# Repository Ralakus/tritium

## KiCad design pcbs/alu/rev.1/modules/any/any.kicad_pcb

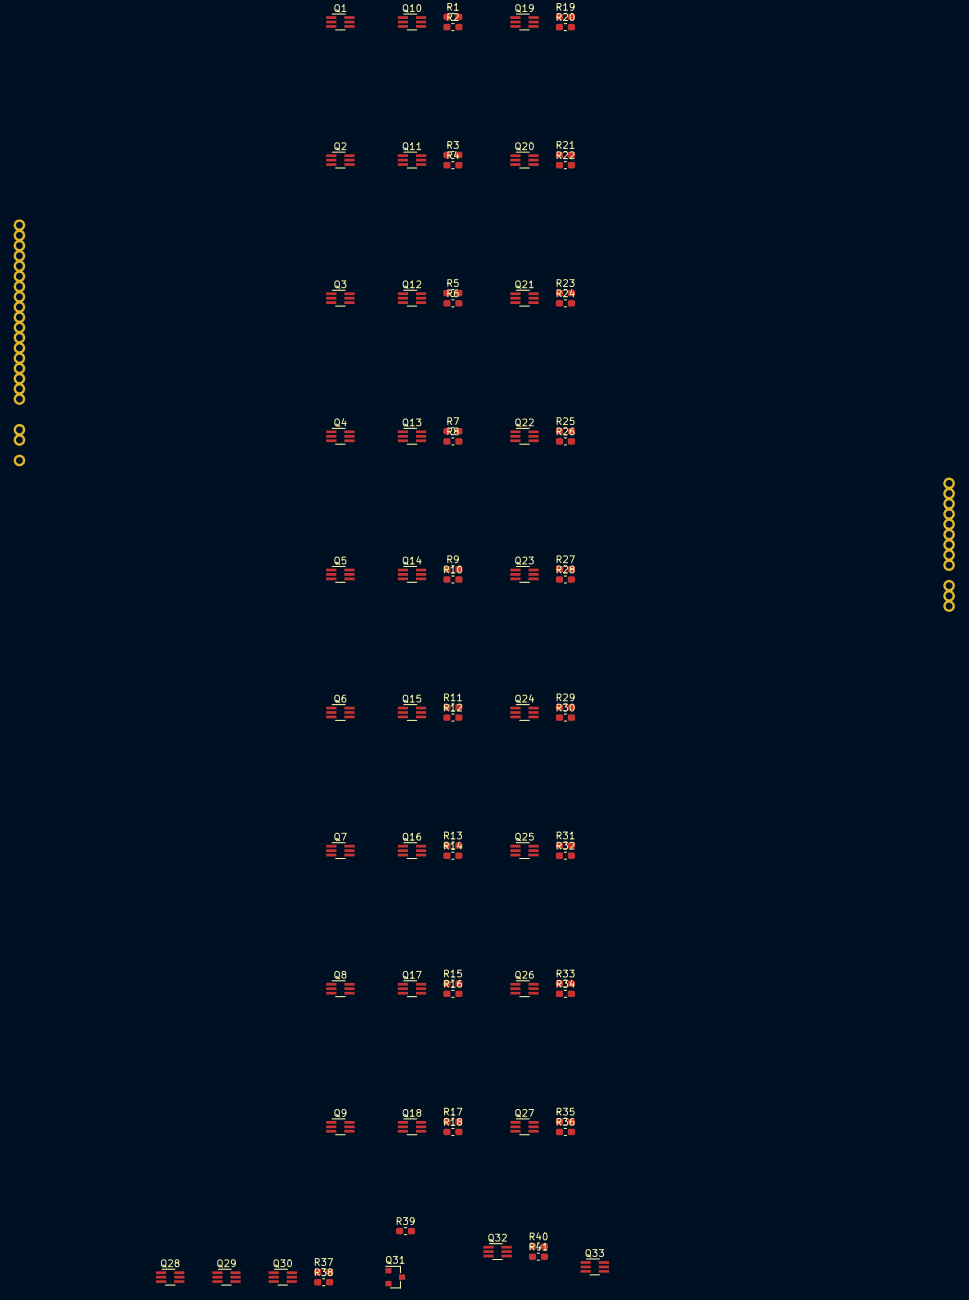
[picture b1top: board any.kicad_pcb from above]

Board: 2 copper layers, 107 parts (0 on the bottom side), 105 nets, no tracks yet.

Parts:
J1, J2, J3, J4, J5, J6, J7, J8, J9, J10, J11, J12, J13, J14, J15, J16, J17, J18, J19, J20, J21, J22, J23, J24, J25, J26, J27, J28, J29, J30, J31, J32, J33: Conn_01x01; Edge_Castellation_1x01_P2.54
Q1, Q2, Q3, Q4, Q5, Q6, Q7, Q8, Q9, Q10, Q11, Q12, Q13, Q14, Q15, Q16, Q17, Q18, Q19, Q20, Q21, Q22, Q23, Q24, Q25, Q26, Q27, Q28, Q29, Q30, Q32, Q33: BSS8402DW; SOT-363_SC-70-6_Handsoldering
Q31: 2N7002; SOT-23
R1, R2, R3, R4, R5, R6, R7, R8, R9, R10, R11, R12, R13, R14, R15, R16, R17, R18, R19, R20, R21, R22, R23, R24, R25, R26, R27, R28, R29, R30, R31, R32, R33, R34, R35, R36, R37, R38, R39, R40, R41: 12k; R_0603_1608Metric_Pad1.05x0.95mm_HandSolder

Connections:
/Sheet5FFC6CCC/Vdd: Q1.4, Q2.4, Q3.4, Q4.4, Q5.4, Q6.4, Q7.4, Q8.4, Q9.4, Q19.4, Q20.4, Q21.4, Q22.4, Q23.4, Q24.4, Q25.4, Q26.4, Q27.4, Q33.3
/Sheet5FFC6CCC/Vss: Q1.1, Q2.1, Q3.1, Q4.1, Q5.1, Q6.1, Q7.1, Q8.1, Q9.1, Q19.1, Q20.1, Q21.1, Q22.1, Q23.1, Q24.1, Q25.1, Q26.1, Q27.1, Q33.6
A0: J1.1, Q9.2, Q9.5
A1: J2.1, Q8.2, Q8.5
A2: J3.1, Q7.2, Q7.5
A3: J4.1, Q6.2, Q6.5
A4: J5.1, Q5.2, Q5.5
A5: J6.1, Q4.2, Q4.5
A6: J7.1, Q3.2, Q3.5
A7: J8.1, Q2.2, Q2.5
A8: J9.1, Q1.2, Q1.5
B0: J10.1, Q18.2, Q18.5
B1: J11.1, Q17.2, Q17.5
B2: J12.1, Q16.2, Q16.5
B3: J13.1, Q15.2, Q15.5
B4: J14.1, Q14.2, Q14.5
B5: J15.1, Q13.2, Q13.5
B6: J16.1, Q12.2, Q12.5
B7: J17.1, Q11.2, Q11.5
B8: J18.1, Q10.2, Q10.5
FnA2: J19.1, Q28.2, Q28.5
FnB2: J20.1, Q29.2, Q29.5
GND: J32.1, Q31.2
unnamed: Q1.3, Q10.4
unnamed: Q1.6, Q10.1
unnamed: Q10.3, R1.2
unnamed: Q10.6, R2.1
unnamed: Q2.6, Q11.1
unnamed: Q11.3, R3.2
unnamed: Q2.3, Q11.4
unnamed: Q11.6, R4.1
unnamed: Q3.6, Q12.1
unnamed: Q12.3, R5.2
unnamed: Q3.3, Q12.4
unnamed: Q12.6, R6.1
unnamed: Q4.6, Q13.1
unnamed: Q13.3, R7.2
unnamed: Q4.3, Q13.4
unnamed: Q13.6, R8.1
unnamed: Q5.6, Q14.1
unnamed: Q14.3, R9.2
unnamed: Q5.3, Q14.4
unnamed: Q14.6, R10.1
unnamed: Q6.6, Q15.1
unnamed: Q15.3, R11.2
unnamed: Q6.3, Q15.4
unnamed: Q15.6, R12.1
unnamed: Q7.6, Q16.1
unnamed: Q16.3, R13.2
unnamed: Q7.3, Q16.4
unnamed: Q16.6, R14.1
unnamed: Q8.6, Q17.1
unnamed: Q17.3, R15.2
unnamed: Q8.3, Q17.4
unnamed: Q17.6, R16.1
unnamed: Q9.6, Q18.1
unnamed: Q18.3, R17.2
unnamed: Q9.3, Q18.4
unnamed: Q18.6, R18.1
unnamed: Q19.2, Q19.5, R1.1, R2.2
unnamed: Q19.3, R19.2
unnamed: Q19.6, R20.1
unnamed: Q20.2, Q20.5, R3.1, R4.2
unnamed: Q20.3, R21.2
unnamed: Q20.6, R22.1
unnamed: Q21.2, Q21.5, R5.1, R6.2
unnamed: Q21.3, R23.2
unnamed: Q21.6, R24.1
unnamed: Q22.2, Q22.5, R7.1, R8.2
unnamed: Q22.3, R25.2
unnamed: Q22.6, R26.1
unnamed: Q23.2, Q23.5, R9.1, R10.2
unnamed: Q23.3, R27.2
unnamed: Q23.6, R28.1
unnamed: Q24.2, Q24.5, R11.1, R12.2
unnamed: Q24.3, R29.2
unnamed: Q24.6, R30.1
unnamed: Q25.2, Q25.5, R13.1, R14.2
unnamed: Q25.3, R31.2
unnamed: Q25.6, R32.1
unnamed: Q26.2, Q26.5, R15.1, R16.2
unnamed: Q26.3, R33.2
unnamed: Q26.6, R34.1
unnamed: Q27.2, Q27.5, R17.1, R18.2
unnamed: Q27.3, R35.2
unnamed: Q27.6, R36.1
unnamed: Q28.3, Q29.3, Q30.3, R37.2
unnamed: Q28.6, Q29.6, Q30.6, R38.1
unnamed: Q31.1, R37.1, R38.2
unnamed: Q31.3, Q32.2, Q32.5, Q33.2, R39.1
unnamed: Q32.3, R40.2
unnamed: Q32.6, R41.1
unnamed: Q33.5, R40.1, R41.2
OutputEnable: J21.1, Q30.2, Q30.5
R0: J22.1, R35.1, R36.2
R1: J23.1, R33.1, R34.2
R2: J24.1, R31.1, R32.2
R3: J25.1, R29.1, R30.2
R4: J26.1, R27.1, R28.2
R5: J27.1, R25.1, R26.2
R6: J28.1, R23.1, R24.2
R7: J29.1, R21.1, R22.2
R8: J30.1, R19.1, R20.2
Vdd: J31.1, Q28.4, Q29.4, Q30.4, Q32.4, Q33.4, R39.2
Vss: J33.1, Q28.1, Q29.1, Q30.1, Q32.1, Q33.1

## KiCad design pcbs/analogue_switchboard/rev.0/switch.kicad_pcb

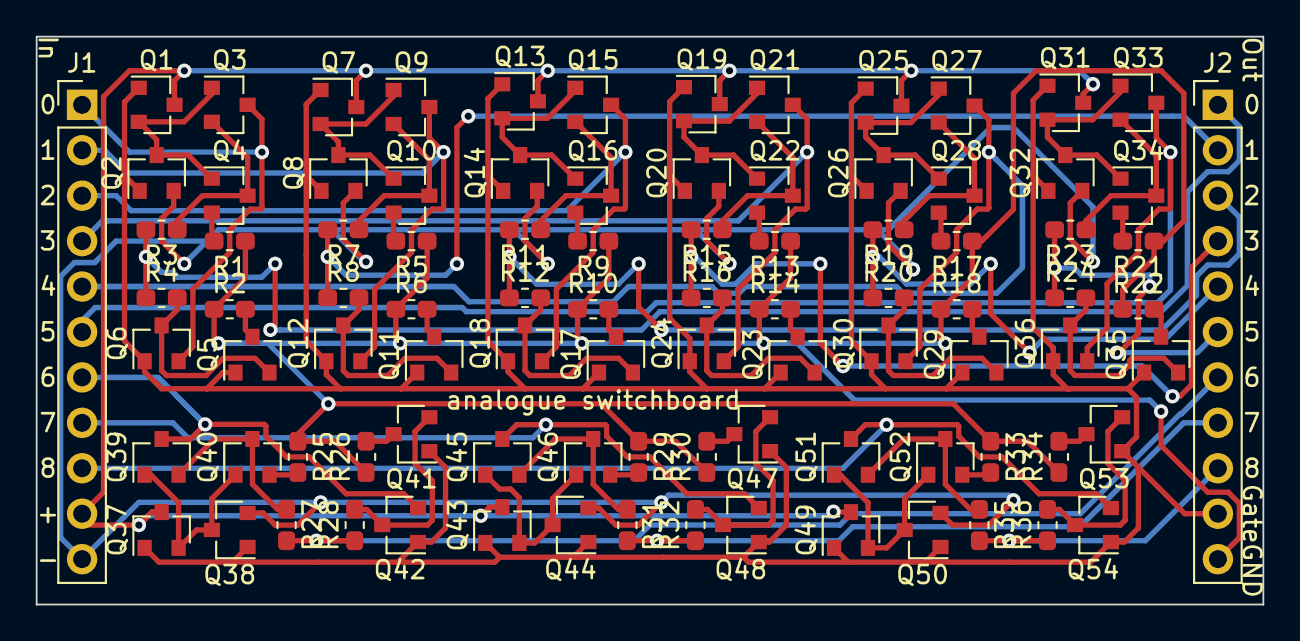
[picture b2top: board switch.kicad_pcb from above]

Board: 2 copper layers, 68.6 x 31.8 mm, 92 parts (0 on the bottom side), 67 nets.

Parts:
J1, J2: Conn_01x11; PinHeader_1x11_P2.54mm_Vertical
Q1, Q3, Q4, Q7, Q9, Q10, Q13, Q15, Q16, Q19, Q21, Q22, Q25, Q27, Q28, Q31, Q33, Q34, Q37, Q39, Q40, Q43, Q45, Q46, Q49, Q51, Q52: BSS84; SOT-23
Q2, Q5, Q6, Q8, Q11, Q12, Q14, Q17, Q18, Q20, Q23, Q24, Q26, Q29, Q30, Q32, Q35, Q36, Q38, Q41, Q42, Q44, Q47, Q48, Q50, Q53, Q54: 2N7002; SOT-23
R1, R2, R3, R4, R5, R6, R7, R8, R9, R10, R11, R12, R13, R14, R15, R16, R17, R18, R19, R20, R21, R22, R23, R24, R25, R26, R27, R28, R29, R30, R31, R32, R33, R34, R35, R36: 12k; R_0603_1608Metric_Pad1.05x0.95mm_HandSolder

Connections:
GND: J2.11, R1.1, R2.1, R5.1, R6.1, R9.1, R10.1, R13.1, R14.1, R17.1, R18.1, R21.1, R22.1, R25.1, R26.1, R29.1, R30.1, R33.1, R34.1
Gate: J2.10, Q1.1, Q2.1, Q5.1, Q6.1, Q7.1, Q8.1, Q11.1, Q12.1, Q13.1, Q14.1, Q17.1, Q18.1, Q19.1, Q20.1, Q23.1, Q24.1, Q25.1, Q26.1, Q29.1, Q30.1, Q31.1, Q32.1, Q35.1, Q36.1, Q37.1, Q38.1, Q41.1, Q42.1, Q43.1, Q44.1, Q47.1, Q48.1, Q49.1, Q50.1, Q53.1, Q54.1
I0: J1.1, Q3.3, Q6.2
I1: J1.2, Q9.3, Q12.2
I2: J1.3, Q15.3, Q18.2
I3: J1.4, Q21.3, Q24.2
I4: J1.5, Q27.3, Q30.2
I5: J1.6, Q33.3, Q36.2
I6: J1.7, Q39.3, Q42.2
I7: J1.8, Q45.3, Q48.2
I8: J1.9, Q51.3, Q54.2
unnamed: Q1.2, Q2.3, Q3.1, Q4.1
unnamed: Q3.2, Q4.3, R3.1
unnamed: Q4.2, R1.2
unnamed: Q5.2, Q6.3, R4.2
unnamed: Q5.3, R2.2
unnamed: Q7.2, Q8.3, Q9.1, Q10.1
unnamed: Q10.2, R5.2
unnamed: Q9.2, Q10.3, R7.1
unnamed: Q11.2, Q12.3, R8.2
unnamed: Q11.3, R6.2
unnamed: Q13.2, Q14.3, Q15.1, Q16.1
unnamed: Q15.2, Q16.3, R11.1
unnamed: Q16.2, R9.2
unnamed: Q17.2, Q18.3, R12.2
unnamed: Q17.3, R10.2
unnamed: Q19.2, Q20.3, Q21.1, Q22.1
unnamed: Q21.2, Q22.3, R15.1
unnamed: Q22.2, R13.2
unnamed: Q23.2, Q24.3, R16.2
unnamed: Q23.3, R14.2
unnamed: Q25.2, Q26.3, Q27.1, Q28.1
unnamed: Q27.2, Q28.3, R19.1
unnamed: Q28.2, R17.2
unnamed: Q29.2, Q30.3, R20.2
unnamed: Q29.3, R18.2
unnamed: Q31.2, Q32.3, Q33.1, Q34.1
unnamed: Q33.2, Q34.3, R23.1
unnamed: Q34.2, R21.2
unnamed: Q35.2, Q36.3, R24.2
unnamed: Q35.3, R22.2
unnamed: Q37.2, Q38.3, Q39.1, Q40.1
unnamed: Q39.2, Q40.3, R27.1
unnamed: Q40.2, R25.2
unnamed: Q41.2, Q42.3, R28.2
unnamed: Q41.3, R26.2
unnamed: Q43.2, Q44.3, Q45.1, Q46.1
unnamed: Q45.2, Q46.3, R31.1
unnamed: Q46.2, R29.2
unnamed: Q47.2, Q48.3, R32.2
unnamed: Q47.3, R30.2
unnamed: Q49.2, Q50.3, Q51.1, Q52.1
unnamed: Q51.2, Q52.3, R35.1
unnamed: Q52.2, R33.2
unnamed: Q53.2, Q54.3, R36.2
unnamed: Q53.3, R34.2
O0: J2.1, R3.2, R4.1
O1: J2.2, R7.2, R8.1
O2: J2.3, R11.2, R12.1
O3: J2.4, R15.2, R16.1
O4: J2.5, R19.2, R20.1
O5: J2.6, R23.2, R24.1
O6: J2.7, R27.2, R28.1
O7: J2.8, R31.2, R32.1
O8: J2.9, R35.2, R36.1
Vdd: J1.10, Q1.3, Q7.3, Q13.3, Q19.3, Q25.3, Q31.3, Q37.3, Q43.3, Q49.3
Vss: J1.11, Q2.2, Q8.2, Q14.2, Q20.2, Q26.2, Q32.2, Q38.2, Q44.2, Q50.2

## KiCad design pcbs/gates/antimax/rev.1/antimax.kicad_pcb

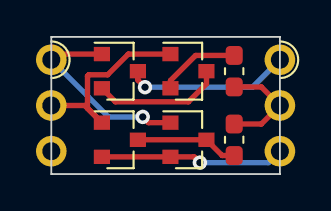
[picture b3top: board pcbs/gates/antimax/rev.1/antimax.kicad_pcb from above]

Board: 2 copper layers, 12.7 x 7.6 mm, 8 parts (0 on the bottom side), 8 nets.

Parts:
J1, J2: Conn_01x03; Edge_Castellation_1x03_P2.54
Q1, Q4: 2N7002; SOT-23
Q2, Q3: BSS84; SOT-23
R1, R2: 12k; R_0603_1608Metric_Pad1.05x0.95mm_HandSolder

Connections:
A: J1.1, Q2.1, Q4.1
B: J1.2, Q1.1, Q3.1
unnamed: Q1.3, Q4.3, R2.2
unnamed: Q2.2, Q3.3
unnamed: Q3.2, R1.1
Out: J2.2, R1.2, R2.1
Vdd: J2.1, Q2.3
Vss: J2.3, Q1.2, Q4.2

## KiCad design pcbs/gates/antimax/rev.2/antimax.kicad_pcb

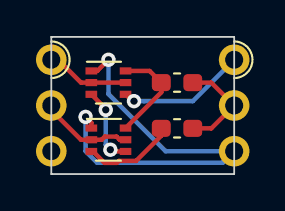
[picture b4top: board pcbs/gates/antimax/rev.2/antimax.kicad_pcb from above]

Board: 2 copper layers, 10.2 x 7.6 mm, 6 parts (0 on the bottom side), 8 nets.

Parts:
J1, J2: Conn_01x03; Edge_Castellation_1x03_P2.54
Q1, Q2: BSS8402DW; SOT-363_SC-70-6
R1, R2: 12k; R_0603_1608Metric_Pad1.05x0.95mm_HandSolder

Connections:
A: J1.1, Q1.2, Q1.5
B: J1.2, Q2.2, Q2.5
unnamed: Q1.3, Q2.4
unnamed: Q1.6, Q2.6, R2.2
unnamed: Q2.3, R1.1
Out: J2.2, R1.2, R2.1
Vdd: J2.1, Q1.4
Vss: J2.3, Q1.1, Q2.1

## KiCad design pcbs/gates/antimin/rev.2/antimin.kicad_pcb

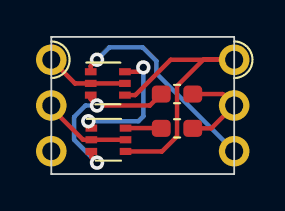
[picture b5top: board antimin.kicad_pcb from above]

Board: 2 copper layers, 10.2 x 7.6 mm, 6 parts (0 on the bottom side), 8 nets.

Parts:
J1, J2: Conn_01x03; Edge_Castellation_1x03_P2.54
Q1, Q2: BSS8402DW; SOT-363_SC-70-6
R1, R2: 12k; R_0603_1608Metric_Pad1.05x0.95mm_HandSolder

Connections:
A: J1.1, Q1.2, Q1.5
B: J1.2, Q2.2, Q2.5
unnamed: Q1.3, Q2.3, R1.1
unnamed: Q1.6, Q2.1
unnamed: Q2.6, R2.2
Out: J2.2, R1.2, R2.1
Vdd: J2.1, Q1.4, Q2.4
Vss: J2.3, Q1.1

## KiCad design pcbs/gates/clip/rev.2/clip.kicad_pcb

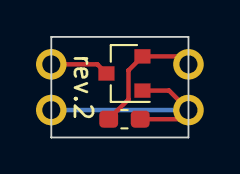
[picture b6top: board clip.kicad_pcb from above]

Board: 2 copper layers, 7.6 x 5.6 mm, 6 parts (0 on the bottom side), 3 nets.

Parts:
J1, J2, J3, J4: Conn_01x01; Edge_Castellation_1x01_P2.54
Q1: BSS84; SOT-23
R1: 470k; R_0603_1608Metric_Pad1.05x0.95mm_HandSolder

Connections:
Anode: J1.1, Q1.3
Cathode: J3.1, Q1.2, R1.1
GND: J2.1, J4.1, Q1.1, R1.2

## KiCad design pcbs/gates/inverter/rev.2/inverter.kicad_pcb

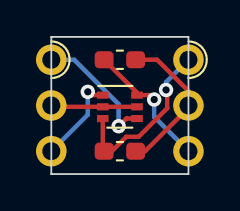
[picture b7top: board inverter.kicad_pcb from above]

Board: 2 copper layers, 7.6 x 7.6 mm, 5 parts (0 on the bottom side), 6 nets.

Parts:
J1, J2: Conn_01x03; Edge_Castellation_1x03_P2.54
Q1: BSS8402DW; SOT-363_SC-70-6
R1, R2: 12k; R_0603_1608Metric_Pad1.05x0.95mm_HandSolder

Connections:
In: J1.2, Q1.2, Q1.5
Nti: J2.3, Q1.6, R2.2
Out: J2.2, R1.2, R2.1
Pti: J2.1, Q1.3, R1.1
Vdd: J1.1, Q1.4
Vss: J1.3, Q1.1

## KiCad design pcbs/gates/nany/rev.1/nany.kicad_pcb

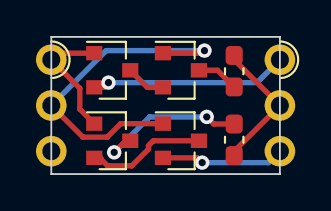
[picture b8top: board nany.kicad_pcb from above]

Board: 2 copper layers, 12.7 x 7.6 mm, 8 parts (0 on the bottom side), 9 nets.

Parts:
J1, J2: Conn_01x03; Edge_Castellation_1x03_P2.54
Q1, Q2: BSS84; SOT-23
Q3, Q4: 2N7002; SOT-23
R1, R2: 12k; R_0603_1608Metric_Pad1.05x0.95mm_HandSolder

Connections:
A: J1.1, Q1.1, Q3.1
B: J1.2, Q2.1, Q4.1
unnamed: Q1.3, Q2.2
unnamed: Q2.3, R1.1
unnamed: Q3.2, Q4.3
unnamed: Q3.3, R2.2
Out: J2.2, R1.2, R2.1
Vdd: J2.1, Q1.2
Vss: J2.3, Q4.2
